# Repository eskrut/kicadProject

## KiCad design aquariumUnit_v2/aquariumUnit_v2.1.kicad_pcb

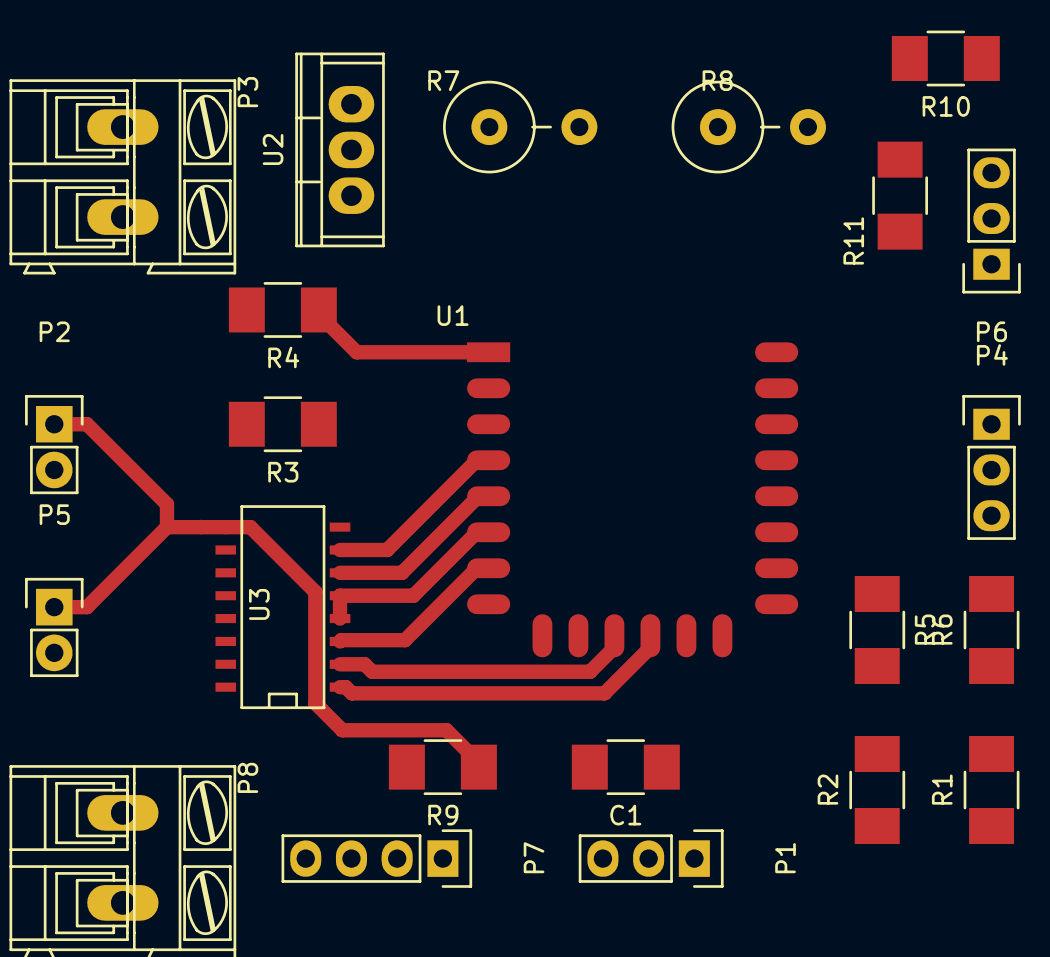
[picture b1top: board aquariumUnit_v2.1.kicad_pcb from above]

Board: 2 copper layers, 23 parts (0 on the bottom side), 24 nets.

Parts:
C1: 0.1uF; C_1210_HandSoldering
P1: SERVO; Pin_Header_Straight_1x03
P2: PUMP; Pin_Header_Straight_1x02
P3: POWER; AK300-2
P4: BUTTONS; Pin_Header_Straight_1x03
P5: FAN; Pin_Header_Straight_1x02
P6: DS; Pin_Header_Straight_1x03
P7: SUB_LEDS; Pin_Header_Straight_1x04
P8: LED_STRIP; AK300-2
R1, R2, R3, R4, R5, R10, R11: 10K; R_1210_HandSoldering
R6: 4.7K; R_1210_HandSoldering
R7: 330; Resistor_Vertical_RM5mm
R8: 560; Resistor_Vertical_RM5mm
R9: 470; R_1210_HandSoldering
U1: ESP-12E
U2: LM317T; TO-220
U3: ULN2003; SO-16-N

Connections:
+3V3: C1.1, P1.2, P4.1, P6.1, R1.1, R3.2, R4.2, R5.1, R6.1, R7.1, U1.8, U2.2
+12V: P2.1, P3.1, P5.1, P8.1, R9.1, U2.3, U3.9
/BT1: P4.2, R10.1, U1.19
/BT2: P4.3, R11.1, U1.20
/D0: P6.2, R1.2, R6.2, U1.18
/D2: P1.1, R5.2, U1.17
/D9: U1.11, U3.2
/D10: U1.12, U3.1
/D12: U1.6, U3.4, U3.5
/D13: U1.7, U3.3
/D14: U1.5, U3.6
/D15: R2.2, U1.16
/D16: U1.4, U3.7
/RST: R4.1, U1.1
GND: C1.2, P1.3, P3.2, P6.3, R2.1, R8.2, R10.2, R11.2, U1.15, U3.8
unnamed: P2.2, U3.10
unnamed: P5.2, U3.11
unnamed: P7.1, R9.2
unnamed: P7.2, U3.16
unnamed: P7.3, U3.15
unnamed: P7.4, U3.14
unnamed: P8.2, U3.12, U3.13
unnamed: R3.1, U1.3
unnamed: R7.2, R8.1, U2.1

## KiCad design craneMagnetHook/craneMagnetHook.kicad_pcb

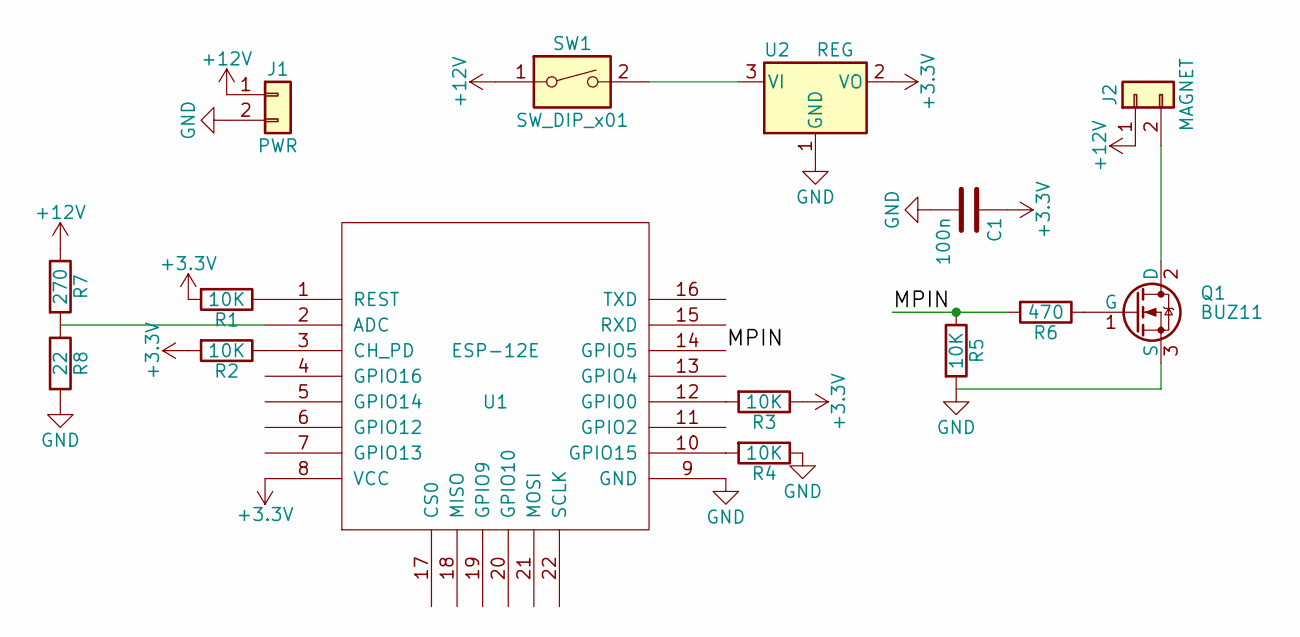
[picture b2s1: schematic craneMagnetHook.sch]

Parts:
C1: 100n; C_1206
J1: PWR; NetTie-I
J2: MAGNET; NetTie-I
Q1: BUZ11; TO-220_Vertical
R1, R2, R3, R4, R5: 10K; R_1206
R6: 470; R_1206
R7: 270; R_1206
R8: 22; R_1206
SW1: SW_DIP_x01; NetTie-I
U1: ESP-12E; ESP-12E_SMD
U2: REG; SOT-223-3Lead_TabPin2

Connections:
+3V3: C1.1, R1.2, R2.2, R3.1, U1.8 (VCC), U2.2 (VO)
+12V: J1.1, J2.1, R7.1, SW1.1
/MPIN: R5.1, R6.2, U1.14 (GPIO5)
GND: C1.2, J1.2, Q1.3 (S), R4.1, R5.2, R8.2, U1.9 (GND), U2.1 (GND)
unnamed: J2.2, Q1.2 (D)
unnamed: Q1.1 (G), R6.1
unnamed: R1.1, U1.1 (REST)
unnamed: R2.1, U1.3 (CH_PD)
unnamed: R3.2, U1.12 (GPIO0)
unnamed: R4.2, U1.10 (GPIO15)
unnamed: R7.2, R8.1, U1.2 (ADC)
unnamed: SW1.2, U2.3 (VI)

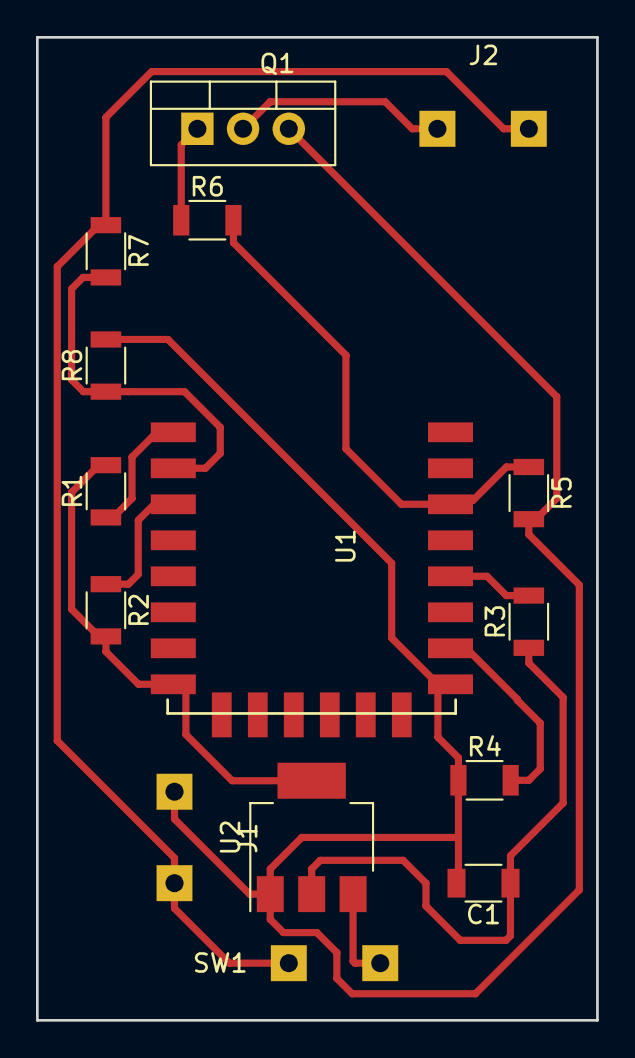
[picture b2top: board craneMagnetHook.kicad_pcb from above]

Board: 2 copper layers, 31.1 x 54.6 mm, 15 parts (0 on the bottom side), 12 nets.

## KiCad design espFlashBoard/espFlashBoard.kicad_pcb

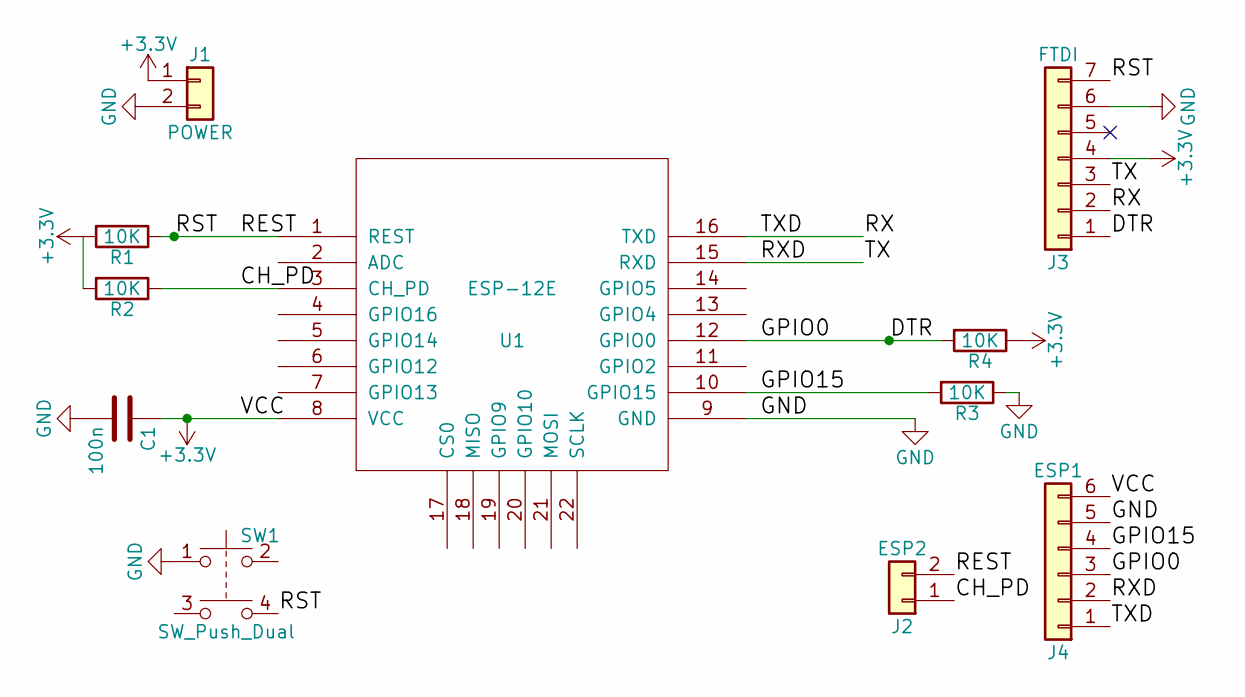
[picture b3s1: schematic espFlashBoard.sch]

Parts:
C1: 100n; C_1206_HandSoldering
J1: POWER; Socket_Strip_Straight_1x02_Pitch2.54mm
J2: ESP2; Socket_Strip_Straight_1x02_Pitch2.54mm
J3: FTDI; Socket_Strip_Straight_1x07_Pitch2.54mm
J4: ESP1; Socket_Strip_Straight_1x06_Pitch2.54mm
R1, R2, R3, R4: 10K; R_1206_HandSoldering
SW1: SW_Push_Dual; NetTie-III
U1: ESP-12E

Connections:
+3V3: C1.1, J1.1, J3.4, J4.6, R1.2, R2.2, R4.1, U1.8 (VCC)
/CH_PD: J2.1, R2.1, U1.3 (CH_PD)
/DTR: J3.1, J4.3, R4.2, U1.12 (GPIO0)
/GPIO15: J4.4, R3.2, U1.10 (GPIO15)
/REST: J2.2, J3.7, R1.1, SW1.4, U1.1 (REST)
/RX: J3.2, J4.1, U1.16 (TXD)
/RXD: J3.3, J4.2, U1.15 (RXD)
GND: C1.2, J1.2, J3.6, J4.5, R3.1, SW1.1, U1.9 (GND)

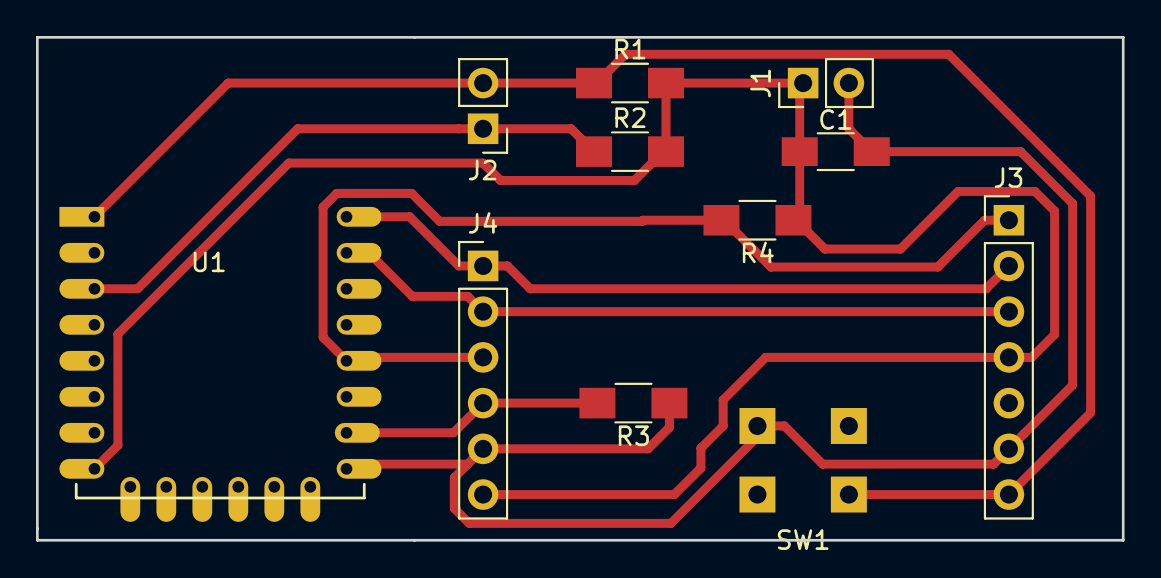
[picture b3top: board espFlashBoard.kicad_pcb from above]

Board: 2 copper layers, 60.3 x 27.9 mm, 11 parts (0 on the bottom side), 8 nets.

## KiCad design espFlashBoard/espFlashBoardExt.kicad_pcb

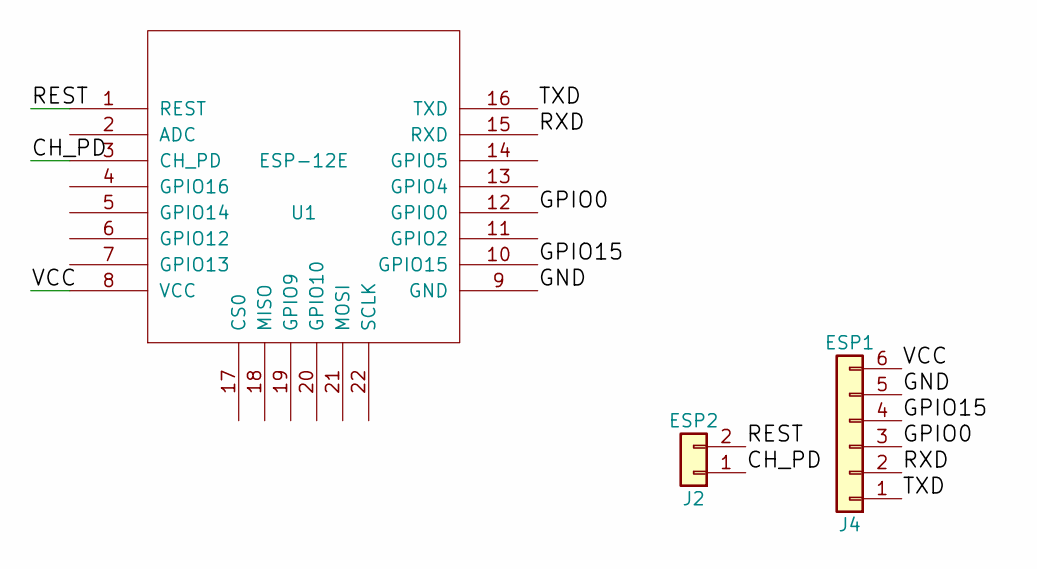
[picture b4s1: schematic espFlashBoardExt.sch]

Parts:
J2: ESP2; Socket_Strip_Straight_1x02_Pitch2.54mm
J4: ESP1; Socket_Strip_Straight_1x06_Pitch2.54mm
U1: ESP-12E

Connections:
/CH_PD: J2.1, U1.3 (CH_PD)
/GND: J4.5, U1.9 (GND)
/GPIO0: J4.3, U1.12 (GPIO0)
/GPIO15: J4.4, U1.10 (GPIO15)
/REST: J2.2, U1.1 (REST)
/RXD: J4.2, U1.15 (RXD)
/TXD: J4.1, U1.16 (TXD)
/VCC: J4.6, U1.8 (VCC)

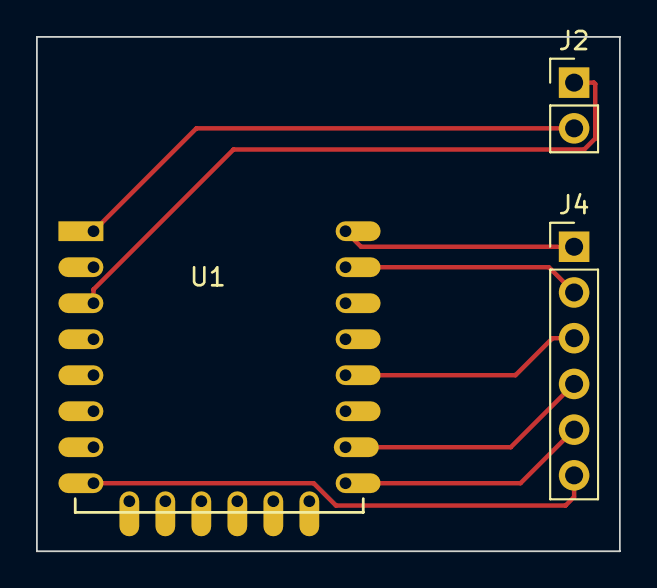
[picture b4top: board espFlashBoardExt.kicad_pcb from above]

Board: 2 copper layers, 32.4 x 28.6 mm, 3 parts (0 on the bottom side), 8 nets.

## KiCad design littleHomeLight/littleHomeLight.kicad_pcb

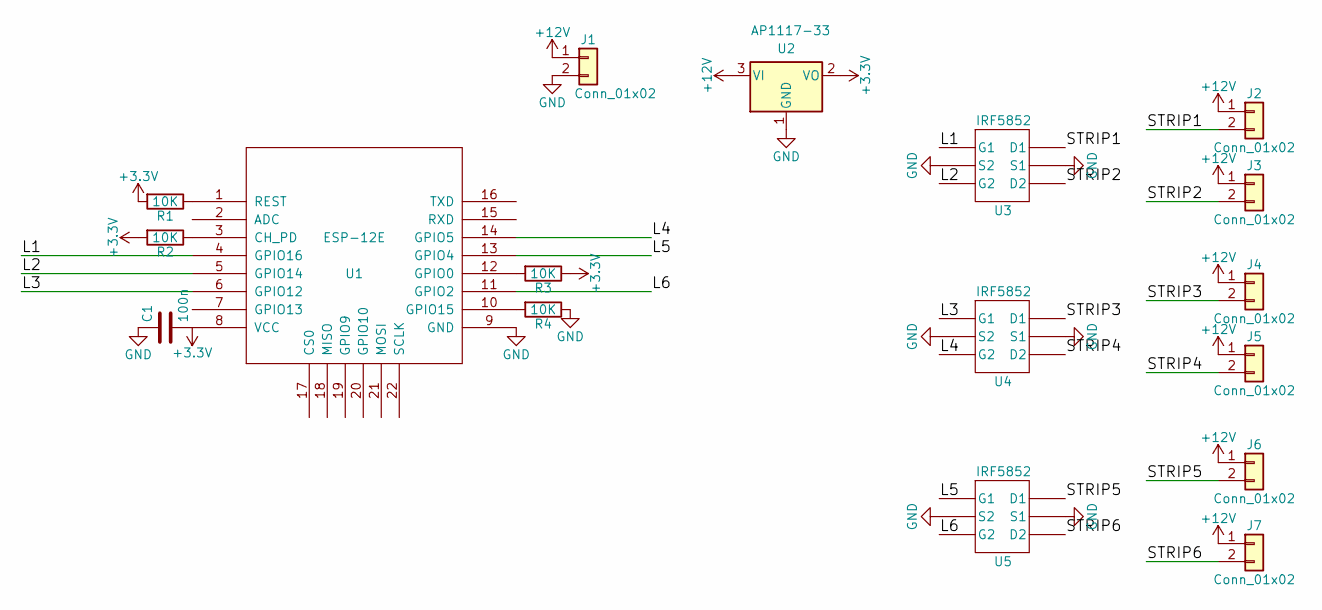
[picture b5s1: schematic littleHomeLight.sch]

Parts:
C1: 100n; C_1206
J1, J2, J3, J4, J5, J6, J7: Conn_01x02; Socket_Strip_Straight_1x02_Pitch2.54mm
R1, R2, R3, R4: 10K; R_1206
U1: ESP-12E; ESP-12E_SMD
U2: AP1117-33; SOT-223-3Lead_TabPin2
U3, U4, U5: IRF5852; SOT-23-6

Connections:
+3V3: C1.2, R1.2, R2.2, R3.1, U1.8 (VCC), U2.2 (VO)
+12V: J1.1, J2.1, J3.1, J4.1, J5.1, J6.1, J7.1, U2.3 (VI)
/L1: U1.4 (GPIO16), U3.1 (G1)
/L2: U1.5 (GPIO14), U3.3 (G2)
/L3: U1.6 (GPIO12), U4.1 (G1)
/L4: U1.14 (GPIO5), U4.3 (G2)
/L5: U1.13 (GPIO4), U5.1 (G1)
/L6: U1.11 (GPIO2), U5.3 (G2)
/STRIP1: J2.2, U3.6 (D1)
/STRIP2: J3.2, U3.4 (D2)
/STRIP3: J4.2, U4.6 (D1)
/STRIP4: J5.2, U4.4 (D2)
/STRIP5: J6.2, U5.6 (D1)
/STRIP6: J7.2, U5.4 (D2)
GND: C1.1, J1.2, R4.1, U1.9 (GND), U2.1 (GND), U3.2 (S2), U3.5 (S1), U4.2 (S2), U4.5 (S1), U5.2 (S2), U5.5 (S1)
unnamed: R1.1, U1.1 (REST)
unnamed: R2.1, U1.3 (CH_PD)
unnamed: R3.2, U1.12 (GPIO0)
unnamed: R4.2, U1.10 (GPIO15)

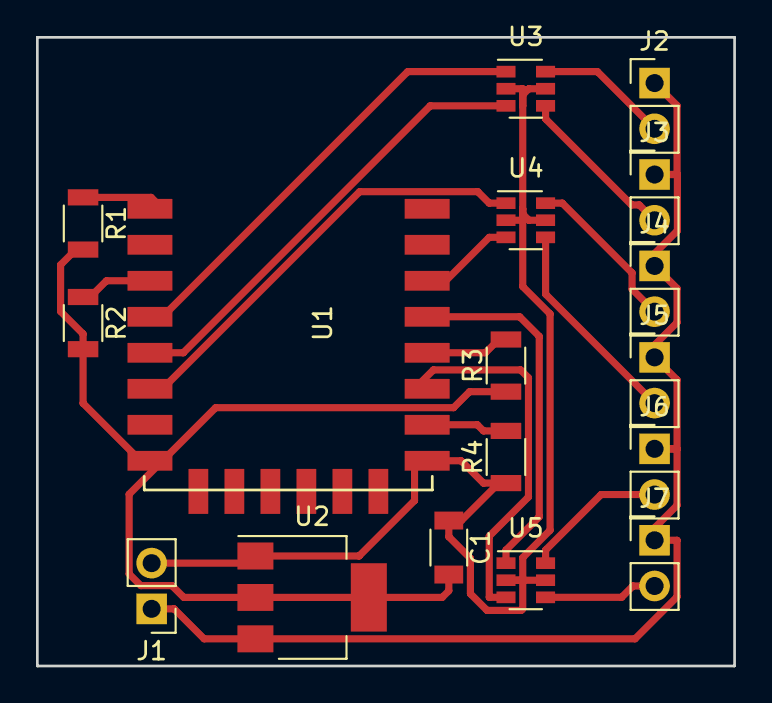
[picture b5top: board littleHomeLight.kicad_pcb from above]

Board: 2 copper layers, 38.7 x 34.9 mm, 17 parts (0 on the bottom side), 19 nets.

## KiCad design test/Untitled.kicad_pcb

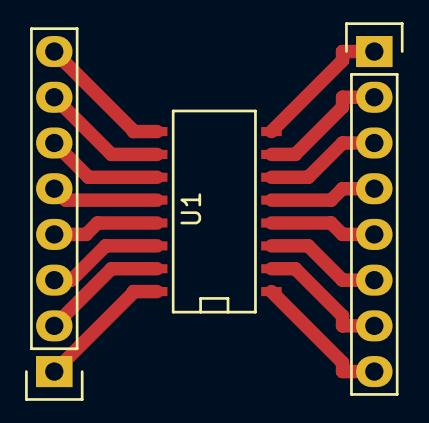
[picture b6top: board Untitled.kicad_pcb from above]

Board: 2 copper layers, 3 parts (0 on the bottom side), 16 nets.

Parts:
P1, P2: CONN_01X08; Pin_Header_Straight_1x08
U1: ULN2003; SO-16-N

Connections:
GND: P1.1, U1.8
unnamed: P1.2, U1.7
unnamed: P1.3, U1.6
unnamed: P1.4, U1.5
unnamed: P1.5, U1.4
unnamed: P1.6, U1.3
unnamed: P1.7, U1.2
unnamed: P1.8, U1.1
unnamed: P2.1, U1.16
unnamed: P2.2, U1.15
unnamed: P2.3, U1.14
unnamed: P2.4, U1.13
unnamed: P2.5, U1.12
unnamed: P2.6, U1.11
unnamed: P2.7, U1.10
unnamed: P2.8, U1.9

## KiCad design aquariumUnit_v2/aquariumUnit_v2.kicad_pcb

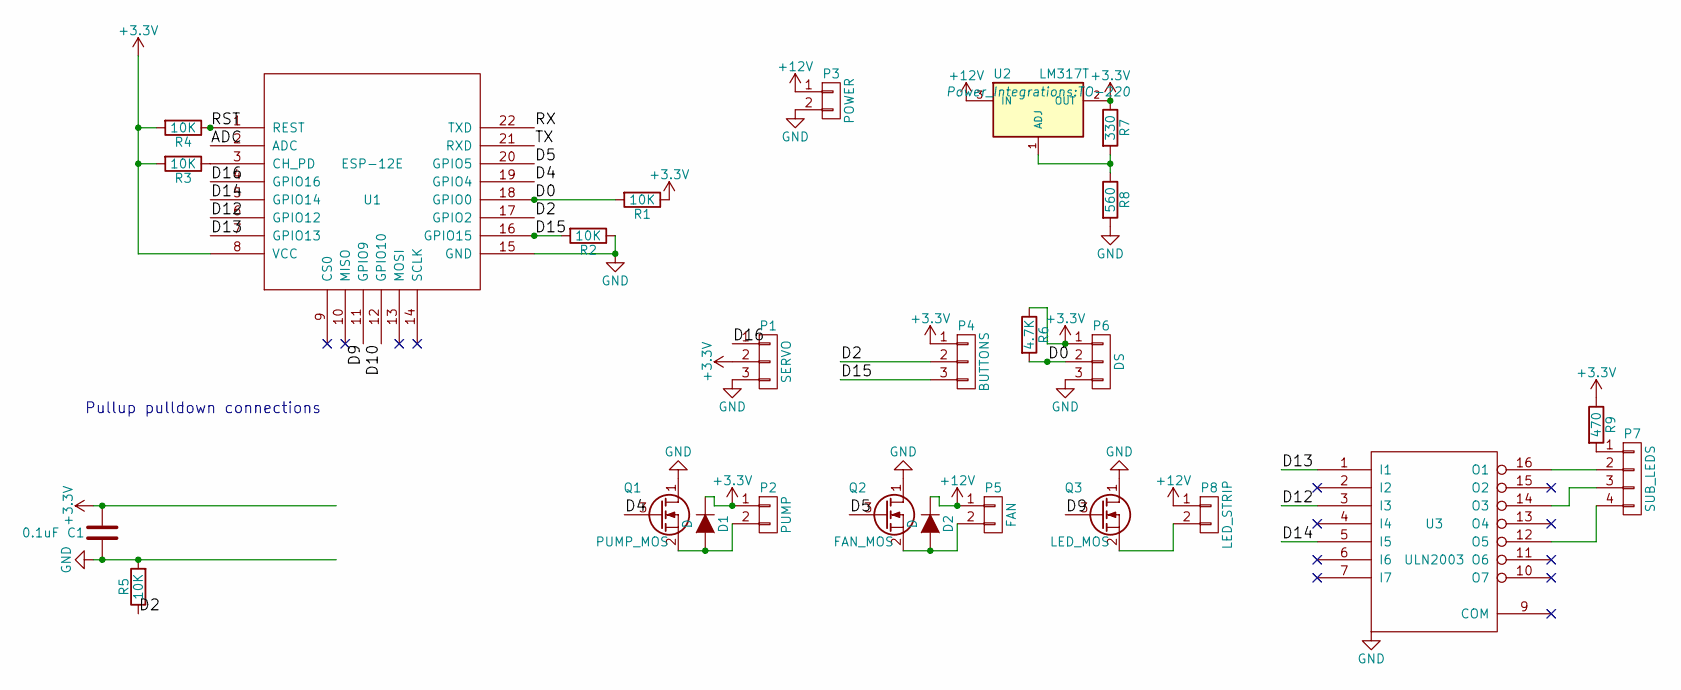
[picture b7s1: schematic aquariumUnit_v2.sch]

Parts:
C1: 0.1uF; C_1210_HandSoldering
D1, D2: D; Diode_DO-35_SOD27_Horizontal_RM10
P1: SERVO; Pin_Header_Straight_1x03
P2: PUMP; Pin_Header_Straight_1x02
P3: POWER; AK300-2
P4: BUTTONS; Pin_Header_Straight_1x03
P5: FAN; Pin_Header_Straight_1x02
P6: DS; Pin_Header_Straight_1x03
P7: SUB_LEDS; Pin_Header_Straight_1x04
P8: LED_STRIP; AK300-2
Q1: PUMP_MOS; TO-220_Neutral123_Vertical
Q2: FAN_MOS; TO-220_Neutral123_Vertical
Q3: LED_MOS; TO-220_Neutral123_Vertical
R1, R2, R3, R4, R5: 10K; R_1210_HandSoldering
R6: 4.7K; R_1210_HandSoldering
R7: 330; Resistor_Vertical_RM5mm
R8: 560; Resistor_Vertical_RM5mm
R9: 470; R_1210_HandSoldering
U1: ESP-12E
U2: LM317T; TO-220
U3: ULN2003; SO-16-N

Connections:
+3V3: C1.1, D1.1 (K), P1.2, P2.1, P4.1, P6.1, R1.1, R3.2, R4.2, R6.1, R7.1, R9.1, U1.8 (VCC), U2.2 (OUT)
+12V: D2.1 (K), P3.1, P5.1, P8.1, U2.3 (IN)
/ADC: U1.2 (ADC)
/D0: P6.2, R1.2, R6.2, U1.18 (GPIO0)
/D2: P4.2, R5.1, U1.17 (GPIO2)
/D4: Q1.3 (G), U1.19 (GPIO4)
/D5: Q2.3 (G), U1.20 (GPIO5)
/D9: Q3.3 (G), U1.11 (GPIO9)
/D10: U1.12 (GPIO10)
/D12: U1.6 (GPIO12), U3.3 (I3)
/D13: U1.7 (GPIO13), U3.1 (I1)
/D14: U1.5 (GPIO14), U3.5 (I5)
/D15: P4.3, R2.2, U1.16 (GPIO15)
/D16: P1.1, U1.4 (GPIO16)
/RST: R4.1, U1.1 (REST)
/RX: U1.22 (TXD)
/TX: U1.21 (RXD)
GND: C1.2, P1.3, P3.2, P6.3, Q1.1 (D), Q2.1 (D), Q3.1 (D), R2.1, R5.2, R8.2, U1.15 (GND), U3.8 (GND)
unnamed: D1.2 (A), P2.2, Q1.2 (S)
unnamed: D2.2 (A), P5.2, Q2.2 (S)
unnamed: P7.1, R9.2
unnamed: P7.2, U3.16 (O1)
unnamed: P7.3, U3.14 (O3)
unnamed: P7.4, U3.12 (O5)
unnamed: P8.2, Q3.2 (S)
unnamed: R3.1, U1.3 (CH_PD)
unnamed: R7.2, R8.1, U2.1 (ADJ)

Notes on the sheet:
Pullup pulldown connections

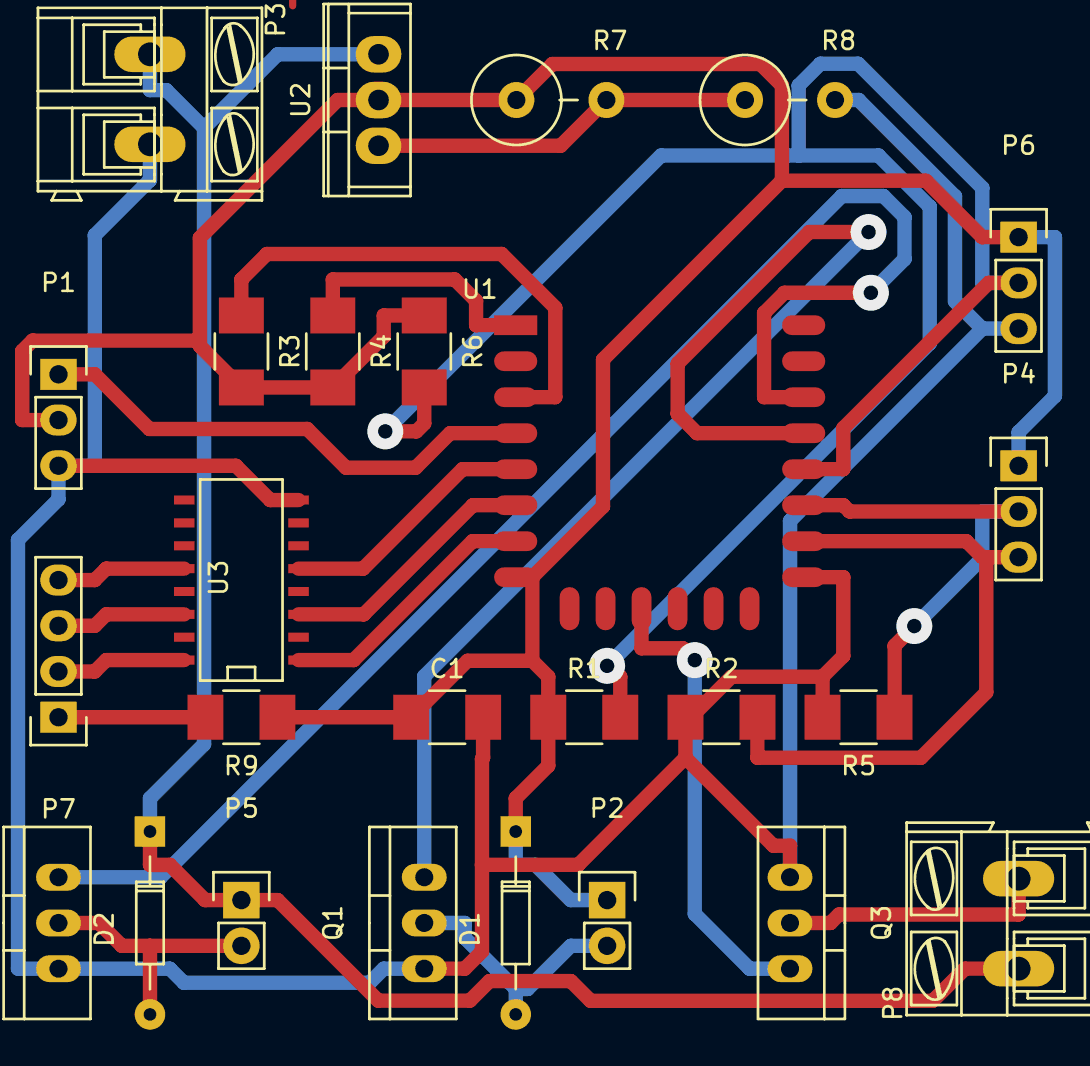
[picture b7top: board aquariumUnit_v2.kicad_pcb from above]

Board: 2 copper layers, 26 parts (0 on the bottom side), 23 nets.

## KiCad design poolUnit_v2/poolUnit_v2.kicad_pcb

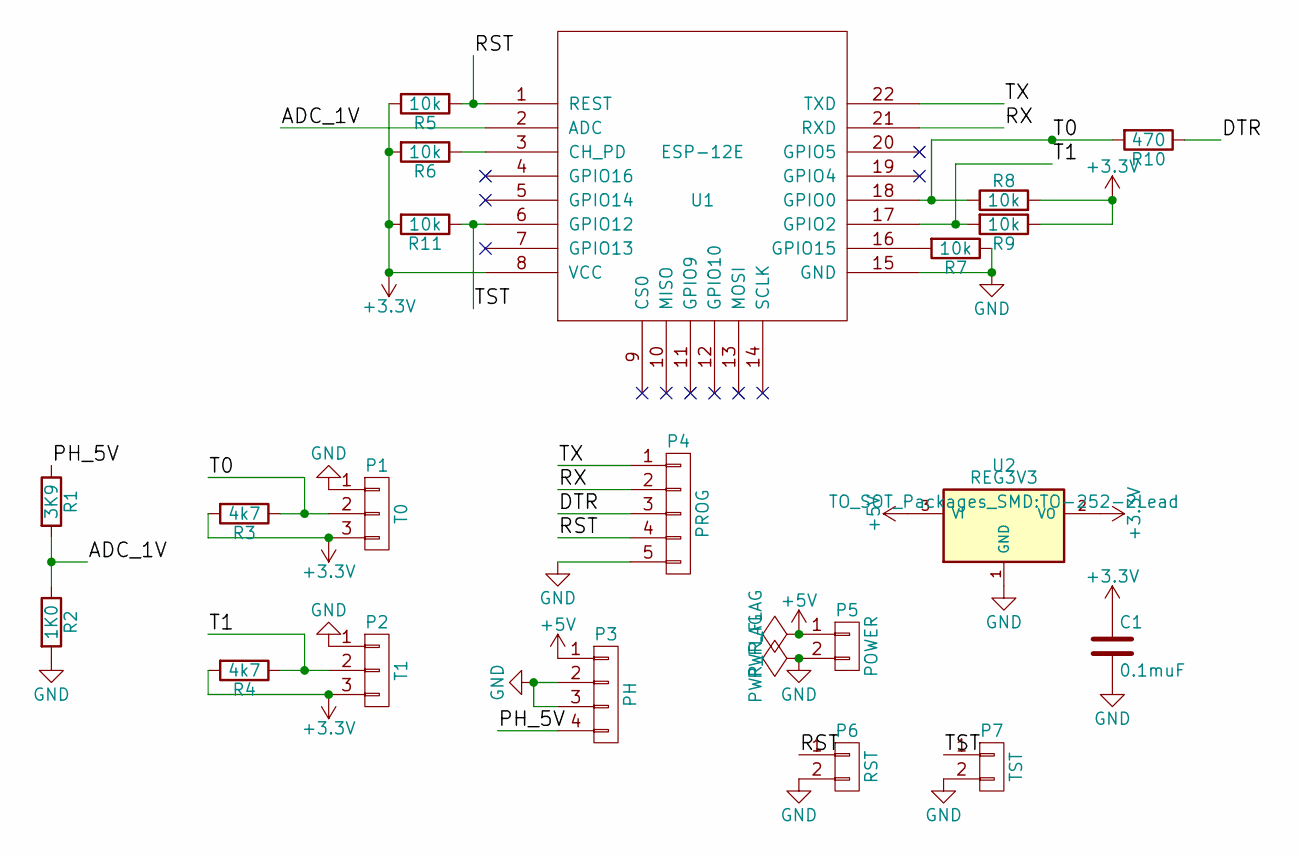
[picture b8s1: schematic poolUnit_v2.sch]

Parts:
C1: 0.1muF; C_1210_HandSoldering
P1: T0; Pin_Header_Straight_1x03
P2: T1; Pin_Header_Straight_1x03
P3: PH; Pin_Header_Straight_1x04
P4: PROG; Pin_Header_Straight_1x05
P5: POWER; Pin_Header_Straight_1x02
P6: RST; Pin_Header_Straight_1x02
P7: TST; Pin_Header_Straight_1x02
R1: 3K9; Resistor_Vertical_RM5mm
R2: 1K0; Resistor_Vertical_RM5mm
R3, R4: 4k7; R_1210_HandSoldering
R5, R6, R7, R8, R9, R11: 10k; R_1210_HandSoldering
R10: 470; R_1210_HandSoldering
U1: ESP-12E
U2: REG3V3; TO-252-2Lead

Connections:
+3V3: C1.1, P1.3, P2.3, R3.2, R4.2, R5.2, R6.2, R8.2, R9.1, R11.2, U1.8 (VCC), U2.2 (VO)
+5V: P3.1, P5.1, U2.3 (VI)
/ADC_1V: R1.2, R2.1, U1.2 (ADC)
/DTR: P4.3, R10.1
/PH_5V: P3.4, R1.1
/RST: P4.4, P6.1, R5.1, U1.1 (REST)
/RX: P4.2, U1.21 (RXD)
/T0: P1.2, R3.1, R8.1, R10.2, U1.18 (GPIO0)
/T1: P2.2, R4.1, R9.2, U1.17 (GPIO2)
/TST: P7.1, R11.1, U1.6 (GPIO12)
/TX: P4.1, U1.22 (TXD)
GND: C1.2, P1.1, P2.1, P3.2, P3.3, P4.5, P5.2, P6.2, P7.2, R2.2, R7.1, U1.15 (GND), U2.1 (GND)
unnamed: R6.1, U1.3 (CH_PD)
unnamed: R7.2, U1.16 (GPIO15)

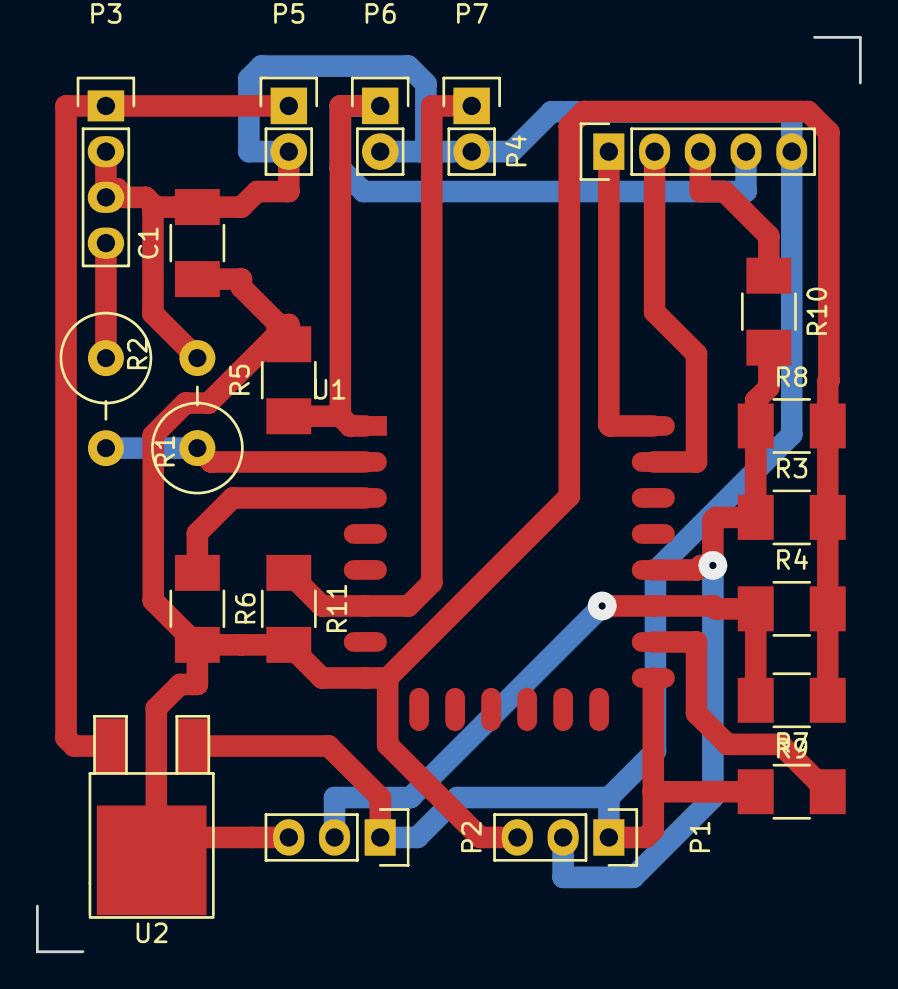
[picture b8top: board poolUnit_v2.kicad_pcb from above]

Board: 2 copper layers, 45.7 x 50.8 mm, 21 parts (0 on the bottom side), 14 nets.

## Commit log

2016-06-06 init
2016-06-06 update aquarium
2016-06-27 Update aquarium unit to version 2.1 with single darlington array
2016-06-29 small update to aq v2.1
2017-09-16 hude update
